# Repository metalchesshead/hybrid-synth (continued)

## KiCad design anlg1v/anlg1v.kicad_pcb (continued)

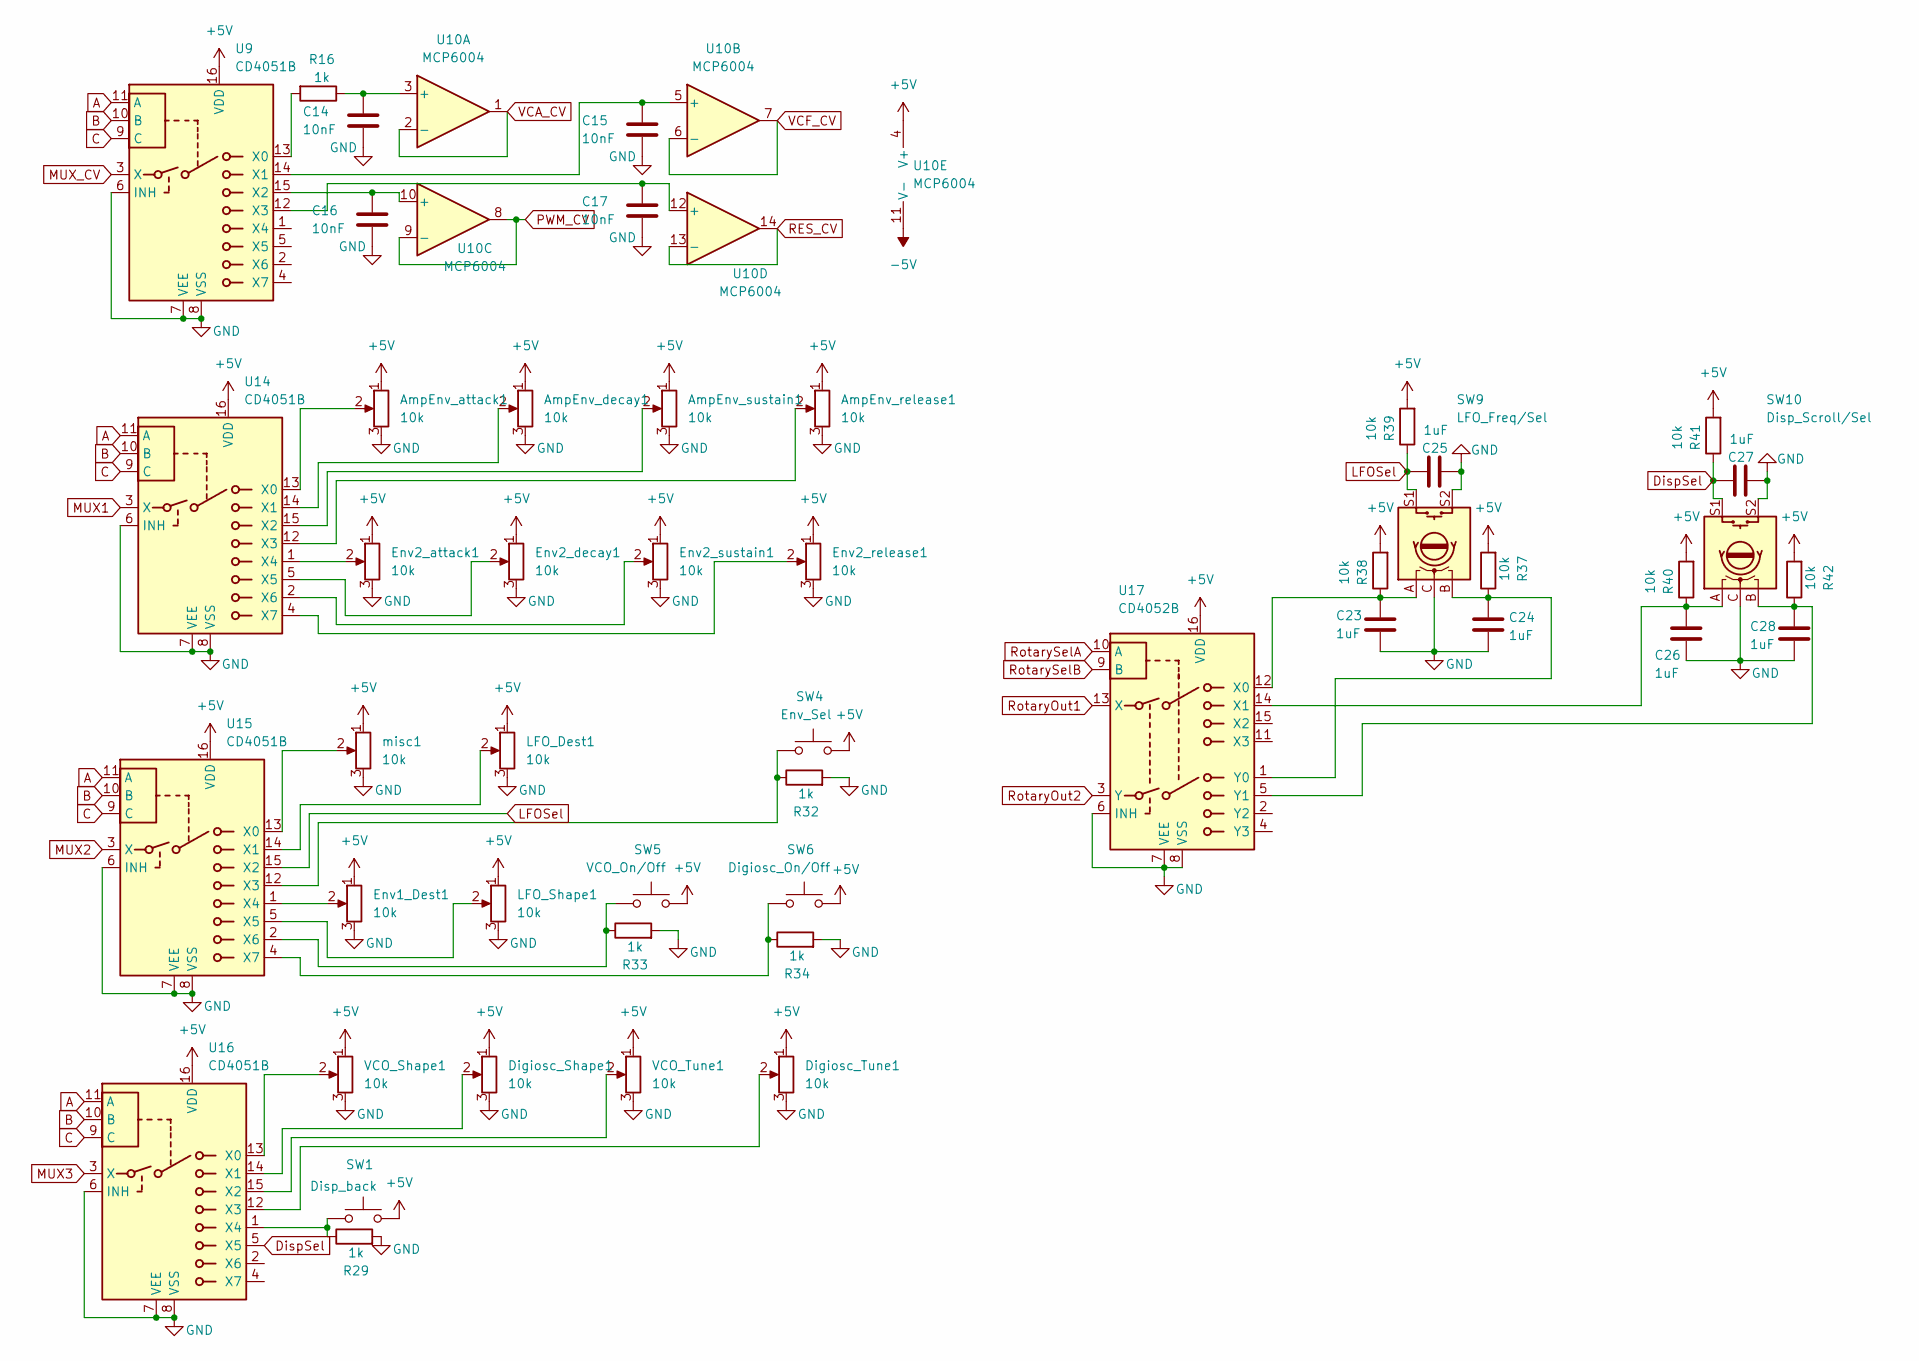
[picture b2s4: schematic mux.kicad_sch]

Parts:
AmpEnv_attack1: 10k; Potentiometer_Bourns_PTA3043_Single_Slide
AmpEnv_decay1: 10k; Potentiometer_Bourns_PTA3043_Single_Slide
AmpEnv_release1: 10k; Potentiometer_Bourns_PTA3043_Single_Slide
AmpEnv_sustain1: 10k; Potentiometer_Bourns_PTA3043_Single_Slide
C14, C15, C16, C17: 10nF; C_0603_1608Metric_Pad1.08x0.95mm_HandSolder
C23, C24, C25, C26, C27, C28: 1uF; C_0603_1608Metric_Pad1.08x0.95mm_HandSolder
Digiosc_Shape1: 10k; Potentiometer_Bourns_PTV09A-1_Single_Vertical
Digiosc_Tune1: 10k; Potentiometer_Bourns_PTV09A-1_Single_Vertical
Env1_Dest1: 10k; Potentiometer_Bourns_PTV09A-1_Single_Vertical
Env2_attack1, Env2_decay1, Env2_release1, Env2_sustain1: 10k; Potentiometer_Bourns_PTA3043_Single_Slide
LFO_Dest1: 10k; Potentiometer_Bourns_PTV09A-1_Single_Vertical
LFO_Shape1: 10k; Potentiometer_Bourns_PTV09A-1_Single_Vertical
R16, R29, R32, R33, R34: 1k; R_0603_1608Metric
R37, R38, R39, R40, R41, R42: 10k; R_0603_1608Metric
SW1: Disp_back; SW_TH_Tactile_Omron_B3F-102x
SW4: Env_Sel; SW_TH_Tactile_Omron_B3F-102x
SW5: VCO_On/Off; SW_TH_Tactile_Omron_B3F-102x
SW6: Digiosc_On/Off; SW_TH_Tactile_Omron_B3F-102x
SW9: LFO_Freq/Sel; RotaryEncoder_Bourns_Vertical_PEC12R-3x17F-Sxxxx
SW10: Disp_Scroll/Sel; RotaryEncoder_Bourns_Vertical_PEC12R-3x17F-Sxxxx
U9, U14, U15, U16: CD4051B; SOIC-16_3.9x9.9mm_P1.27mm
U10: MCP6004; SOIC-14_3.9x8.7mm_P1.27mm
U17: CD4052B; SOIC-16_3.9x9.9mm_P1.27mm
VCO_Shape1: 10k; Potentiometer_Bourns_PTV09A-1_Single_Vertical
VCO_Tune1: 10k; Potentiometer_Bourns_PTV09A-1_Single_Vertical
misc1: 10k; Potentiometer_Bourns_PTV09A-1_Single_Vertical

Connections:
+5V: AmpEnv_attack1.1, AmpEnv_decay1.1, AmpEnv_release1.1, AmpEnv_sustain1.1, Digiosc_Shape1.1, Digiosc_Tune1.1, Env1_Dest1.1, Env2_attack1.1, Env2_decay1.1, Env2_release1.1, Env2_sustain1.1, LFO_Dest1.1, LFO_Shape1.1, R37.2, R38.2, R39.2, R40.2, R41.2, R42.2, SW1.2, SW4.2, SW5.2, SW6.2, U9.16 (VDD), U10.4 (V+), U14.16 (VDD), U15.16 (VDD), U16.16 (VDD), U17.16 (VDD), VCO_Shape1.1, VCO_Tune1.1, misc1.1; also elsewhere on the board
-5V: U10.11 (V-); also elsewhere on the board
A: U9.11 (A), U14.11 (A), U15.11 (A), U16.11 (A); also elsewhere on the board
B: U9.10 (B), U14.10 (B), U15.10 (B), U16.10 (B); also elsewhere on the board
C: U9.9 (C), U14.9 (C), U15.9 (C), U16.9 (C); also elsewhere on the board
DispSel: C27.2, R41.1, SW10.S1, U16.5 (X5)
GND: AmpEnv_attack1.3, AmpEnv_decay1.3, AmpEnv_release1.3, AmpEnv_sustain1.3, C14.2, C15.2, C16.2, C17.2, C23.2, C24.2, C25.1, C26.2, C27.1, C28.2, Digiosc_Shape1.3, Digiosc_Tune1.3, Env1_Dest1.3, Env2_attack1.3, Env2_decay1.3, Env2_release1.3, Env2_sustain1.3, LFO_Dest1.3, LFO_Shape1.3, R29.2, R32.2, R33.2, R34.2, SW9.C, SW9.S2, SW10.C, SW10.S2, U9.6 (INH), U9.7 (VEE), U9.8 (VSS), U14.6 (INH), U14.7 (VEE), U14.8 (VSS), U15.6 (INH), U15.7 (VEE), U15.8 (VSS), U16.6 (INH), U16.7 (VEE), U16.8 (VSS), U17.6 (INH), U17.7 (VEE), U17.8 (VSS), VCO_Shape1.3, VCO_Tune1.3, misc1.3; also elsewhere on the board
LFOSel: C25.2, R39.1, SW9.S1, U15.15 (X2)
MUX1: U14.3 (X); also elsewhere on the board
MUX2: U15.3 (X); also elsewhere on the board
MUX3: U16.3 (X); also elsewhere on the board
MUX_CV: U9.3 (X); also elsewhere on the board
unnamed: R16.2, U9.13 (X0)
unnamed: C14.1, R16.1, U10.3 (+)
unnamed: C15.1, U9.14 (X1), U10.5 (+)
unnamed: C16.1, U9.15 (X2), U10.10 (+)
unnamed: C17.1, U9.12 (X3), U10.12 (+)
unnamed: AmpEnv_attack1.2, U14.13 (X0)
unnamed: AmpEnv_decay1.2, U14.14 (X1)
unnamed: AmpEnv_sustain1.2, U14.15 (X2)
unnamed: AmpEnv_release1.2, U14.12 (X3)
unnamed: Env2_attack1.2, U14.1 (X4)
unnamed: Env2_decay1.2, U14.5 (X5)
unnamed: Env2_sustain1.2, U14.2 (X6)
unnamed: Env2_release1.2, U14.4 (X7)
unnamed: U15.13 (X0), misc1.2
unnamed: LFO_Dest1.2, U15.14 (X1)
unnamed: R32.1, SW4.1, U15.12 (X3)
unnamed: Env1_Dest1.2, U15.1 (X4)
unnamed: LFO_Shape1.2, U15.5 (X5)
unnamed: R33.1, SW5.1, U15.2 (X6)
unnamed: R34.1, SW6.1, U15.4 (X7)
unnamed: U16.13 (X0), VCO_Shape1.2
unnamed: Digiosc_Shape1.2, U16.14 (X1)
unnamed: U16.15 (X2), VCO_Tune1.2
unnamed: Digiosc_Tune1.2, U16.12 (X3)
unnamed: R29.1, SW1.1, U16.1 (X4)
unnamed: C23.1, R38.1, SW9.A, U17.12 (X0)
unnamed: C26.1, R40.1, SW10.A, U17.14 (X1)
unnamed: C24.1, R37.1, SW9.B, U17.1 (Y0)
unnamed: C28.1, R42.1, SW10.B, U17.5 (Y1)
PWM_CV: U10.8, U10.9 (-)
RES_CV: U10.13 (-), U10.14; also elsewhere on the board
RotaryOut1: U17.13 (X); also elsewhere on the board
RotaryOut2: U17.3 (Y); also elsewhere on the board
RotarySelA: U17.10 (A); also elsewhere on the board
RotarySelB: U17.9 (B); also elsewhere on the board
VCA_CV: U10.1, U10.2 (-); also elsewhere on the board
VCF_CV: U10.6 (-), U10.7; also elsewhere on the board

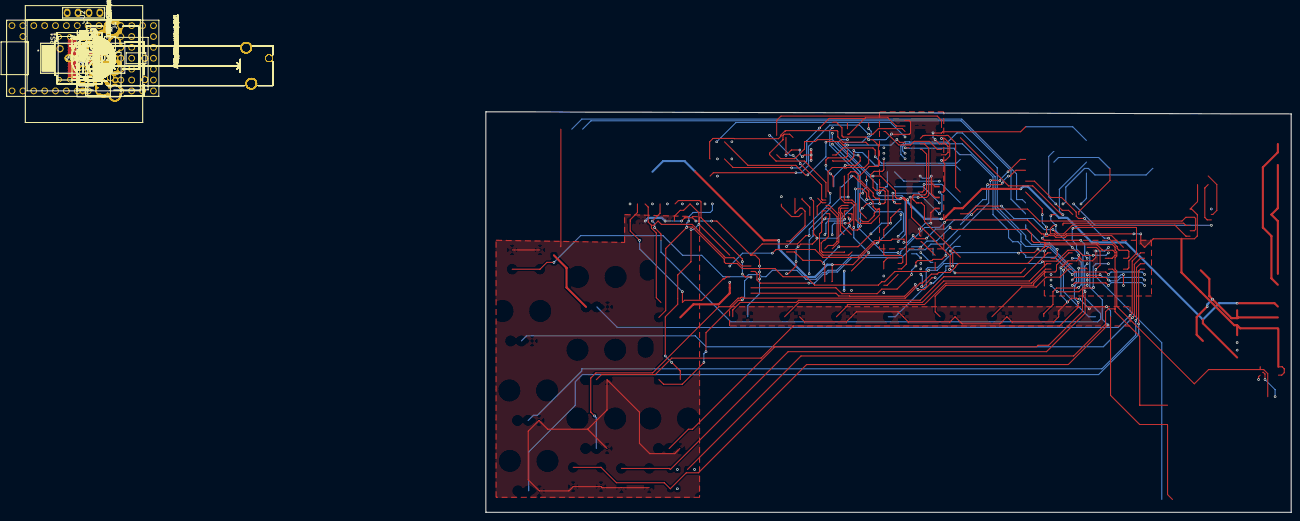
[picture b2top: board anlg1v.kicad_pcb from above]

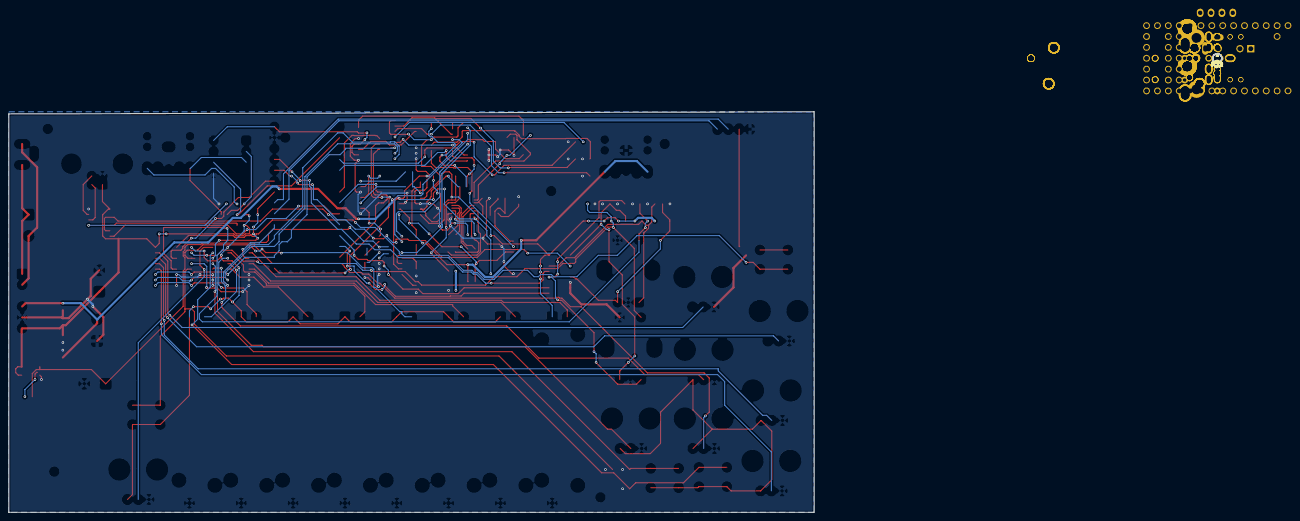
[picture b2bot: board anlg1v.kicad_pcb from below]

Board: 2 copper layers, 188.0 x 93.5 mm, 114 parts (6 on the bottom side), 109 nets.

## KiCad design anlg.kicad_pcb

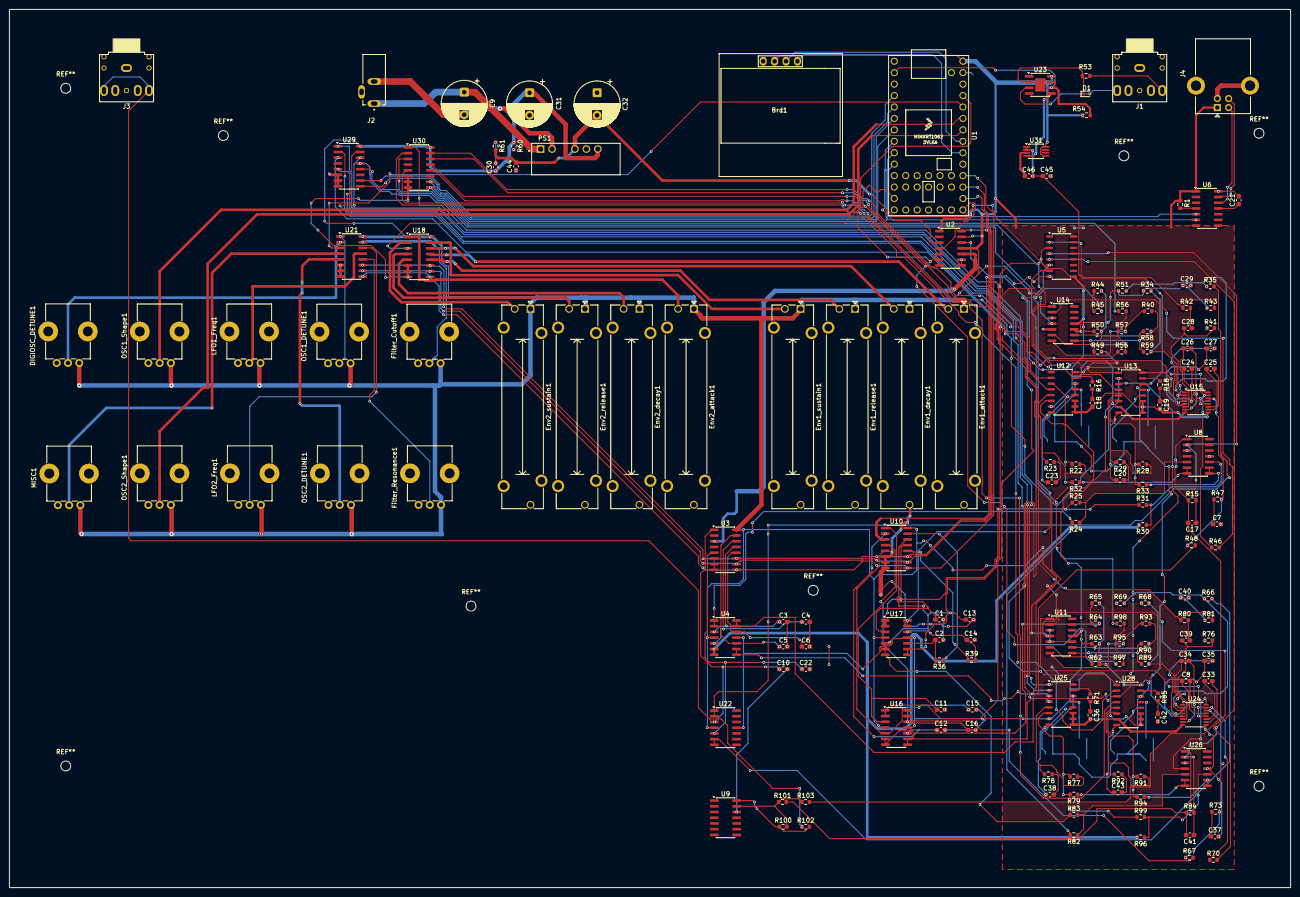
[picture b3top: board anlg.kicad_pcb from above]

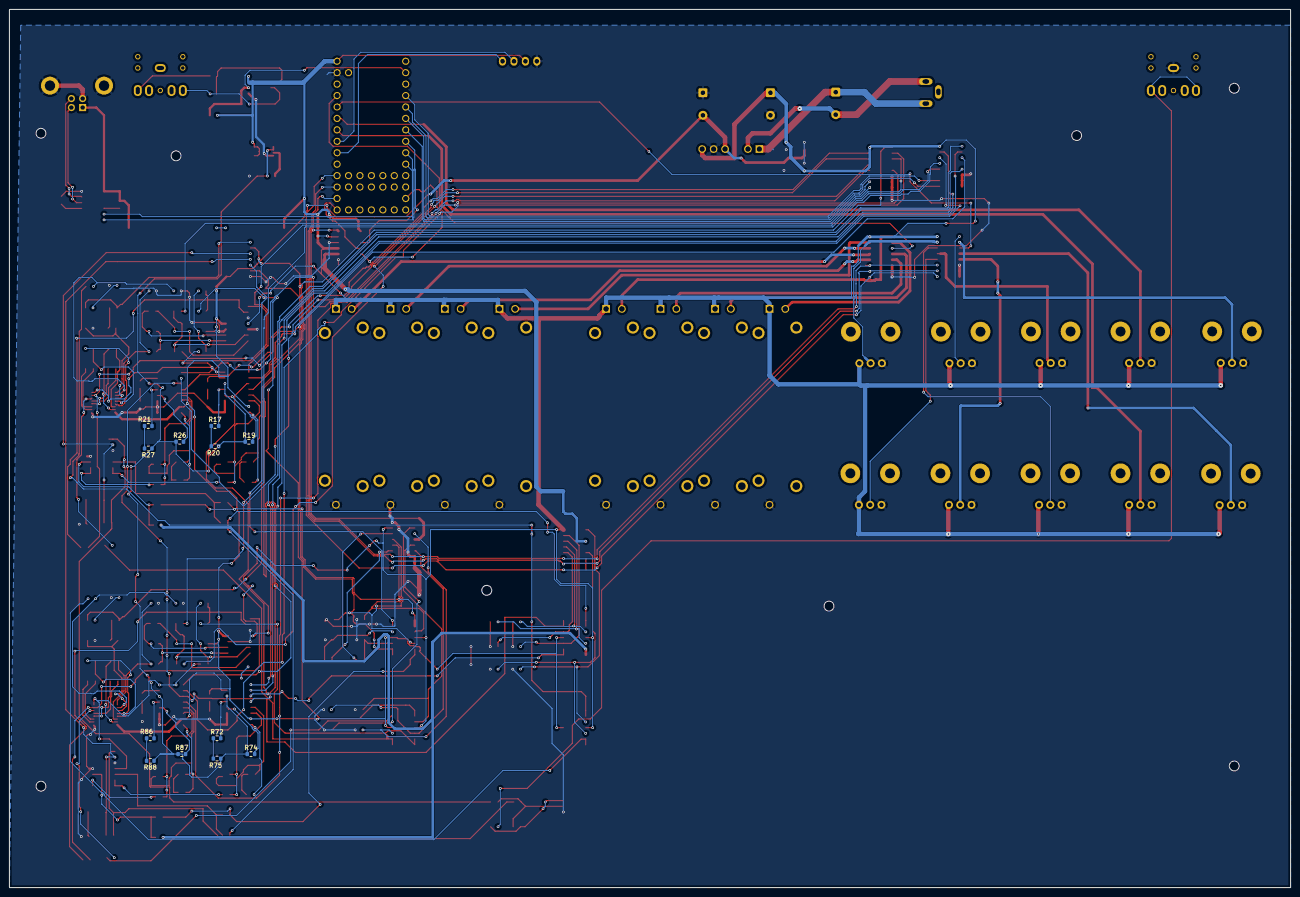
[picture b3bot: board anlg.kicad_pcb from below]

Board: 2 copper layers, 284.5 x 195.0 mm, 185 parts (12 on the bottom side), 195 nets.

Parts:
Brd1: SSD1306; 128x64OLED
C1, C2, C3, C4, C5, C6, C7, C10, C11, C12, C13, C14, C15, C16, C22, C37: 10nF; C_0603_1608Metric_Pad1.08x0.95mm_HandSolder
C8, C24, C25, C26, C33, C34: 6.8nF; C_0603_1608Metric_Pad1.08x0.95mm_HandSolder
C9: 1uF; CP_Radial_D10.0mm_P5.00mm
C17, C41, C46: 100pF; C_0603_1608Metric_Pad1.08x0.95mm_HandSolder
C18, C19, C20, C23, C36, C38, C42, C43: 2.2n; C_0603_1608Metric_Pad1.08x0.95mm_HandSolder
C21: 0.47; C_0603_1608Metric_Pad1.08x0.95mm_HandSolder
C27, C29, C35, C40: 560pF; C_0603_1608Metric_Pad1.08x0.95mm_HandSolder
C28, C39, C45: 10uF; C_0603_1608Metric_Pad1.08x0.95mm_HandSolder
C30, C44: 100nF; C_0603_1608Metric_Pad1.08x0.95mm_HandSolder
C31, C32: 10uF; CP_Radial_D10.0mm_P5.00mm
D1: 1N4148WT; D_SOD-523
DIGIOSC_DETUNE1: 10k; Potentiometer_Bourns_PTV09A-1_Single_Vertical
Env1_attack1, Env1_decay1, Env1_release1, Env1_sustain1, Env2_attack1, Env2_decay1, Env2_release1, Env2_sustain1: 10k; Potentiometer_Bourns_PTA3043_Single_Slide
Filter_Cutoff1: 10k; Potentiometer_Bourns_PTV09A-1_Single_Vertical
Filter_Resonance1: 10k; Potentiometer_Bourns_PTV09A-1_Single_Vertical
J1, J3: AudioJack3; PJ-307
J2: PJ-007; SAMESKY_PJ-007
J4: USB_B; USB_B_Lumberg_2411_02_Horizontal
LFO1_Freq1, LFO2_Freq1: 10k; Potentiometer_Bourns_PTV09A-1_Single_Vertical
MISC1: 10k; Potentiometer_Bourns_PTV09A-1_Single_Vertical
OSC1_DETUNE1, OSC1_Shape1, OSC2_DETUNE1, OSC2_Shape1: 10k; Potentiometer_Bourns_PTV09A-1_Single_Vertical
PS1: RD-0505D; CONV_RD-0505D
R1, R23, R29, R50, R63, R78, R92: 10k; R_0603_1608Metric
R15, R16, R18, R20, R27, R71, R75, R84, R85, R88: 20k; R_0603_1608Metric
R17, R21, R72, R86: 4.7k; R_0603_1608Metric
R19, R26, R74, R87: 499k; R_0603_1608Metric
R22, R28, R77, R91: 200k; R_0603_1608Metric
R24, R30, R49, R62, R82, R96: 30k; R_0603_1608Metric
R25, R31, R83, R99: 50k; R_0603_1608Metric
R32, R33, R48, R67, R79, R94: 22k; R_0603_1608Metric
R34, R51, R68, R69: 200; R_0603_1608Metric
R35, R66: 47k; R_0603_1608Metric
R36, R39, R42, R46, R59, R70, R80, R89, R102: 1k; R_0603_1608Metric
R40, R44, R45, R55, R56, R57, R58, R64, R65, R90, R93, R95, R97, R98, R100, R101, R103: 100k; R_0603_1608Metric
R41, R43, R76, R81: 5.1k; R_0603_1608Metric
R47, R73: 560; R_0603_1608Metric
R53, R60, R61: 220; R_0603_1608Metric
R54: 470; R_0603_1608Metric
U1: Teensy4.0; Teensy40
U2: MCP4922; SOIC-14_3.9x8.7mm_P1.27mm
U3, U10, U18, U21: CD4051B; SOIC-16_3.9x9.9mm_P1.27mm
U4, U8, U16, U17, U22, U26: MCP6004; SOIC-14_3.9x8.7mm_P1.27mm
U5: SSI2164; STC_SOP-16_3.9x9.9mm_P1.27mm
U6: MCP2221AxSL; SOIC-14_3.9x8.7mm_P1.27mm
U9, U11, U14: TL074; SOIC-14_3.9x8.7mm_P1.27mm
U12, U13, U25, U28: SSI2131; STC_SOP-16_3.9x9.9mm_P1.27mm
U15, U24: SSI2144; SSOP-16_3.9x4.9mm_P0.635mm
U23: 6N138; SOIC-8-1EP_3.9x4.9mm_P1.27mm_EP2.29x3mm
U29, U30: CD4052B; SOIC-16_3.9x9.9mm_P1.27mm
U31: LT1962-2.5; MSOP-8_3x3mm_P0.65mm

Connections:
+5V: Brd1.2 (VCC), C30.1, C31.1, DIGIOSC_DETUNE1.1, Env1_attack1.1, Env1_decay1.1, Env1_release1.1, Env1_sustain1.1, Env2_attack1.1, Env2_decay1.1, Env2_release1.1, Env2_sustain1.1, Filter_Cutoff1.1, Filter_Resonance1.1, J4.1 (VBUS), LFO1_Freq1.1, LFO2_Freq1.1, MISC1.1, OSC1_DETUNE1.1, OSC1_Shape1.1, OSC2_DETUNE1.1, OSC2_Shape1.1, PS1.6 (+VOUT), R1.1, R49.2, R54.1, R60.1, R62.2, U1.33 (VIN), U2.1 (Vdd), U2.11 (VrefB), U2.13 (VrefA), U3.16 (VDD), U4.4 (V+), U5.16 (V+), U6.1 (VDD), U8.4 (V+), U10.16 (VDD), U11.4 (V+), U12.16 (V+), U13.16 (V+), U14.4 (V+), U15.16 (V+), U16.4 (V+), U17.4 (V+), U18.16 (VDD), U21.16 (VDD), U22.4 (V+), U23.8 (VCC), U24.16 (V+), U25.16 (V+), U26.4 (V+), U28.16 (V+), U29.16 (VDD), U30.16 (VDD), U31.5 (~SHDN), U31.8 (IN)
-5V: C32.2, C44.2, PS1.4 (-VOUT), R50.1, R61.2, R63.1, U4.11 (V-), U5.9 (V-), U11.11 (V-), U12.7 (V-), U13.7 (V-), U14.11 (V-), U15.8 (V-), U16.11 (V-), U17.11 (V-), U22.11 (V-), U24.8 (V-), U25.7 (V-), U28.7 (V-)
A: U1.21 (14_A0_TX3_SPDIF_OUT), U3.11 (A), U10.11 (A), U18.11 (A), U21.11 (A)
B: U1.22 (15_A1_RX3_SPDIF_IN), U3.10 (B), U10.10 (B), U18.10 (B), U21.10 (B)
C: U1.23 (16_A2_RX4_SCL1), U3.9 (C), U10.9 (C), U18.9 (C), U21.9 (C)
DAC1: U2.14 (VA), U10.3 (X)
DAC2: U2.10 (VB), U3.3 (X)
DIGIOSC_1: R35.2, U22.1, U22.2 (-)
DIGIOSC_2: R66.2, U22.6 (-), U22.7
GND: Brd1.1 (GND), C1.2, C2.2, C3.2, C4.2, C5.2, C6.2, C7.2, C10.2, C11.2, C12.2, C13.2, C14.2, C15.2, C16.2, C18.2, C19.2, C21.2, C22.2, C29.2, C30.2, C31.2, C32.1, C36.2, C37.2, C40.2, C42.2, C44.1, C45.2, DIGIOSC_DETUNE1.3, Env1_attack1.3, Env1_decay1.3, Env1_release1.3, Env1_sustain1.3, Env2_attack1.3, Env2_decay1.3, Env2_release1.3, Env2_sustain1.3, Filter_Cutoff1.3, Filter_Resonance1.3, J3.S, J4.4 (GND), J4.5 (Shield), LFO1_Freq1.3, LFO2_Freq1.3, MISC1.3, OSC1_DETUNE1.3, OSC1_Shape1.3, OSC2_DETUNE1.3, OSC2_Shape1.3, PS1.5 (COM), R34.1, R41.1, R51.1, R60.2, R61.1, R68.1, R69.1, R76.1, U1.32 (GND), U2.8 (~LDAC), U2.9 (~SHDN), U2.12 (Vss), U5.8 (GND), U6.14 (VSS), U8.3 (+), U8.11 (V-), U9.12 (+), U10.6 (INH), U10.7 (VEE), U10.8 (VSS), U11.3 (+), U11.5 (+), U11.10 (+), U12.9 (GND), U12.10 (HARD_SYNC), U12.11 (SOFT_SYNC), U13.9 (GND), U13.10 (HARD_SYNC), U13.11 (SOFT_SYNC), U14.3 (+), U14.5 (+), U14.10 (+), U15.9 (GND), U18.6 (INH), U18.7 (VEE), U18.8 (VSS), U21.6 (INH), U21.7 (VEE), U21.8 (VSS), U23.5 (GND), U24.9 (GND), U25.9 (GND), U25.10 (HARD_SYNC), U25.11 (SOFT_SYNC), U26.3 (+), U26.11 (V-), U28.9 (GND), U28.10 (HARD_SYNC), U28.11 (SOFT_SYNC), U29.6 (INH), U29.7 (VEE), U29.8 (VSS), U30.6 (INH), U30.7 (VEE), U30.8 (VSS), U31.4 (GND)
unnamed: Brd1.3 (SCL), U1.26 (19_A5_SCL0)
unnamed: Brd1.4 (SDA), U1.25 (18_A4_SDA0)
unnamed: C7.1, R47.1
unnamed: C18.1, R16.2
unnamed: C19.1, R18.2
unnamed: C20.2, R29.1
unnamed: C23.2, R23.1
unnamed: C28.2, R42.2
unnamed: C29.1, R43.1
unnamed: C36.1, R71.2
unnamed: C37.1, R73.1
unnamed: C38.2, R78.1
unnamed: C39.2, R80.2
unnamed: C40.1, R81.1
unnamed: C42.1, R85.2
unnamed: C43.2, R92.1
unnamed: D1.2 (A), J1.T, U23.3 (C2)
unnamed: D1.1 (K), R53.1, U23.2 (C1)
unnamed: J1.R, R53.2
unnamed: J3.R, J3.T, R102.1
unnamed: J4.3 (D+), U6.13 (D+)
unnamed: J4.2 (D-), U6.12 (D-)
unnamed: C9.1, J2.1, PS1.1 (+VIN)
unnamed: C9.2, J2.2, PS1.2 (-VIN)
unnamed: R17.1, R20.2
unnamed: R21.1, R27.2
unnamed: R40.1, R57.2, U14.7
unnamed: R42.1, R43.2, U5.2
unnamed: R44.2, R49.1, R50.2
unnamed: R58.2, R59.1, U14.8
unnamed: R62.1, R63.2, R65.2
unnamed: R72.1, R75.2
unnamed: R80.1, R81.2, U5.7
unnamed: R86.1, R88.2
unnamed: R89.1, R90.2, U11.8
unnamed: R93.1, R95.2, U11.7
unnamed: R100.1, R102.2, U9.14
unnamed: R54.2, U1.2 (0_RX1_CRX2_CS1), U23.6 (VO2)
unnamed: U1.8 (6_OUT1D), U2.3 (~CS)
unnamed: U1.13 (11_MOSI_CTX1), U2.5 (SDI)
unnamed: U1.20 (13_SCK_CRX1_LED), U2.4 (SCK)
unnamed: OSC2_Shape1.2, U1.27 (20_A6_TX5_LRCLK1)
unnamed: OSC1_Shape1.2, U1.28 (21_A7_RX5_BCLK1)
unnamed: U3.6 (INH), U3.7 (VEE), U3.8 (VSS)
unnamed: C3.1, U3.13 (X0), U4.3 (+)
unnamed: C4.1, U3.14 (X1), U4.5 (+)
unnamed: C5.1, U3.15 (X2), U4.10 (+)
unnamed: C6.1, U3.12 (X3), U4.12 (+)
unnamed: C21.1, U6.11 (VUSB)
unnamed: R1.2, U6.4 (~RST)
unnamed: C17.1, R15.2, U5.4, U8.2 (-)
unnamed: R24.1, R25.2, U8.5 (+)
unnamed: R32.1, U8.6 (-), U8.7
unnamed: R30.1, R31.2, U8.10 (+)
unnamed: R33.1, U8.8, U8.9 (-)
unnamed: R100.2, R101.1, R103.1, U9.13 (-)
unnamed: C1.1, U10.13 (X0), U17.3 (+)
unnamed: C13.1, U10.14 (X1), U17.5 (+)
unnamed: R36.1, U10.15 (X2)
unnamed: R39.1, U10.12 (X3)
unnamed: C11.1, U10.1 (X4), U16.3 (+)
unnamed: C15.1, U10.5 (X5), U16.5 (+)
unnamed: C12.1, U10.2 (X6), U16.10 (+)
unnamed: C16.1, U10.4 (X7), U16.12 (+)
unnamed: R64.1, R65.1, R70.2, U11.2 (-)
unnamed: R95.1, R97.2, R98.2, U11.6 (-)
unnamed: R90.1, R93.2, U11.9 (-)
unnamed: R16.1, U12.15 (BW_COMP)
unnamed: R22.2, R32.2, U12.6 (EXPO_FREQ)
unnamed: R17.2, U12.13 (EXPO_SCALE)
unnamed: R22.1, R23.2, U12.5 (HF_TRACK)
unnamed: R19.2, U12.12 (LIN_FREQ)
unnamed: C23.1, U12.8 (TCAP)
unnamed: R18.1, U13.15 (BW_COMP)
unnamed: R28.2, R33.2, U13.6 (EXPO_FREQ)
unnamed: R21.2, U13.13 (EXPO_SCALE)
unnamed: R28.1, R29.2, U13.5 (HF_TRACK)
unnamed: R26.2, U13.12 (LIN_FREQ)
unnamed: C20.1, U13.8 (TCAP)
unnamed: R44.1, R45.1, R46.2, U14.2 (-)
unnamed: R55.2, R56.2, R57.1, U14.6 (-)
unnamed: R40.2, R58.1, U14.9 (-)
unnamed: C24.1, U15.13 (C1A)
unnamed: C24.2, U15.12 (C1B)
unnamed: C25.1, U15.11 (C2A)
unnamed: C25.2, U15.10 (C2B)
unnamed: C26.1, U15.6 (C3A)
unnamed: C26.2, U15.7 (C3B)
unnamed: C27.1, U15.4 (C4A)
unnamed: C27.2, U15.5 (C4B)
unnamed: R46.1, U14.1, U15.15 (FREQ_CTRL)
unnamed: C28.1, R41.2, U15.3 (OUT)
unnamed: R47.2, R48.1, U15.14 (Q_CTRL)
unnamed: R35.1, R51.2, U15.2 (SIG_IN-)
unnamed: C2.1, R36.2, U17.10 (+)
unnamed: C14.1, R39.2, U17.12 (+)
unnamed: Env1_attack1.2, U18.13 (X0)
unnamed: Env1_decay1.2, U18.14 (X1)
unnamed: Env1_sustain1.2, U18.15 (X2)
unnamed: Env1_release1.2, U18.12 (X3)
unnamed: Env2_attack1.2, U18.1 (X4)
unnamed: Env2_decay1.2, U18.5 (X5)
unnamed: Env2_sustain1.2, U18.2 (X6)
unnamed: Env2_release1.2, U18.4 (X7)
unnamed: LFO1_Freq1.2, U21.13 (X0)
unnamed: LFO2_Freq1.2, U21.14 (X1)
unnamed: Filter_Cutoff1.2, U21.15 (X2)
unnamed: Filter_Resonance1.2, U21.12 (X3)
unnamed: OSC1_DETUNE1.2, U21.1 (X4)
unnamed: OSC2_DETUNE1.2, U21.5 (X5)
unnamed: DIGIOSC_DETUNE1.2, U21.2 (X6)
unnamed: MISC1.2, U21.4 (X7)
unnamed: C10.1, U3.1 (X4), U22.3 (+)
unnamed: C22.1, U3.5 (X5), U22.5 (+)
unnamed: C8.1, U24.13 (C1A)
unnamed: C8.2, U24.12 (C1B)
unnamed: C33.1, U24.11 (C2A)
unnamed: C33.2, U24.10 (C2B)
unnamed: C34.1, U24.6 (C3A)
unnamed: C34.2, U24.7 (C3B)
unnamed: C35.1, U24.4 (C4A)
unnamed: C35.2, U24.5 (C4B)
unnamed: R70.1, U11.1, U24.15 (FREQ_CTRL)
unnamed: C39.1, R76.2, U24.3 (OUT)
unnamed: R67.1, R73.2, U24.14 (Q_CTRL)
unnamed: R66.1, R69.2, U24.2 (SIG_IN-)
unnamed: R71.1, U25.15 (BW_COMP)
unnamed: R77.2, R79.2, U25.6 (EXPO_FREQ)
unnamed: R72.2, U25.13 (EXPO_SCALE)
unnamed: R77.1, R78.2, U25.5 (HF_TRACK)
unnamed: R74.2, U25.12 (LIN_FREQ)
unnamed: C38.1, U25.8 (TCAP)
unnamed: C41.1, R84.2, U5.5, U26.2 (-)
unnamed: R82.1, R83.2, U26.5 (+)
unnamed: R79.1, U26.6 (-), U26.7
unnamed: R96.1, R99.2, U26.10 (+)
unnamed: R94.1, U26.8, U26.9 (-)
unnamed: R85.1, U28.15 (BW_COMP)
unnamed: R91.2, R94.2, U28.6 (EXPO_FREQ)
unnamed: R86.2, U28.13 (EXPO_SCALE)
unnamed: R91.1, R92.2, U28.5 (HF_TRACK)
unnamed: R87.2, U28.12 (LIN_FREQ)
unnamed: C43.1, U28.8 (TCAP)
unnamed: C46.1, U31.3 (BYP)
OSC1V1PULSE1: U12.2 (PULSE_OUT), U29.14 (X1)
OSC1V1SAW: U12.1 (SAW_OUT), U29.12 (X0)
OSC1V1TRI: U12.4 (TRI_OUT), U29.15 (X2)
OSC1V1_OUT: R55.1, U29.3 (Y)
OSC1V2PULSE1: U25.2 (PULSE_OUT), U29.5 (Y1)
OSC1V2SAW: U25.1 (SAW_OUT), U29.1 (Y0)
OSC1V2TRI: U25.4 (TRI_OUT), U29.2 (Y2)
OSC1V2_OUT: R98.1, U29.13 (X)
OSC1_TUNE: R24.2, R82.2, U4.1, U4.2 (-)
OSC2V1PULSE1: U13.2 (PULSE_OUT), U30.14 (X1)
OSC2V1SAW: U13.1 (SAW_OUT), U30.12 (X0)
OSC2V1TRI: U13.4 (TRI_OUT), U30.15 (X2)
OSC2V1_OUT: R56.1, U30.3 (Y)
OSC2V2PULSE1: U28.2 (PULSE_OUT), U30.5 (Y1)
OSC2V2SAW: U28.1 (SAW_OUT), U30.1 (Y0)
OSC2V2TRI: U28.4 (TRI_OUT), U30.2 (Y2)
OSC2V2_OUT: R97.1, U30.13 (X)
OSC2_TUNE: R30.2, R96.2, U4.6 (-), U4.7
OSCv1SUM_OUT: R34.2, R59.2, U15.1 (SIG_IN+)
OSCv2SUM_OUT: R68.2, R89.2, U24.1 (SIG_IN+)
POTS_IN: U1.30 (23_A9_CRX1_MCLK1), U18.3 (X)
POTS_IN2: U1.29 (22_A8_CTX1), U21.3 (X)
PWMCV_1: U4.8, U4.9 (-), U12.3 (PWM_CTRL), U25.3 (PWM_CTRL)
PWMCV_2: U4.13 (-), U4.14, U13.3 (PWM_CTRL), U28.3 (PWM_CTRL)
REF2V5: C45.1, C46.2, R19.1, R20.1, R26.1, R27.1, R74.1, R75.1, R87.1, R88.1, U12.14 (VREF), U13.14 (VREF), U25.14 (VREF), U28.14 (VREF), U31.1 (OUT), U31.2 (SENSE)
RES_CV1: R48.2, U16.8, U16.9 (-)
RES_CV2: R67.2, U16.13 (-), U16.14
USB_rx: U1.10 (8_TX2_IN1), U6.5 (URx)
USB_tx: U1.9 (7_RX2_OUT1A), U6.6 (UTx)
V1_OUT: C17.2, R15.1, R103.2, U8.1
V2_OUT: C41.2, R84.1, R101.2, U26.1
VCA_CV1: U5.3, U17.8, U17.9 (-)
VCA_CV2: U5.6, U17.13 (-), U17.14
VCF_CV1: R45.2, U16.1, U16.2 (-)
VCF_CV2: R64.2, U16.6 (-), U16.7
VCO_CV1: R25.1, R31.1, U17.1, U17.2 (-)
VCO_CV2: R83.1, R99.1, U17.6 (-), U17.7
WAVESELA1: U1.4 (2_OUT2), U29.10 (A)
WAVESELA2: U1.6 (4_BCLK2), U30.10 (A)
WAVESELB1: U1.5 (3_LRCLK2), U29.9 (B)
WAVESELB2: U1.7 (5_IN2), U30.9 (B)

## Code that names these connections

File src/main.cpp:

#include <MIDI.h>
#include <SPI.h>
#include <Arduino.h>
#include <Wire.h>

#include <EEPROM.h>
#include "header.h"
#include "lut.h"
#include "displaystuff.h"
#include <HardwareSerial.h>
#include <usb_serial.h>
#include <Adafruit_SSD1306.h>

#include <Audio.h>

MIDI_CREATE_INSTANCE(HardwareSerial, Serial1, MIDI); 


#include <Audio.h>
#include <Wire.h>
#include <SPI.h>
#include <SD.h>
#include <SerialFlash.h>

// GUItool: begin automatically generated code
AudioSynthNoisePink      pink1;          //xy=192.20000076293945,360.2000026702881
AudioSynthNoiseWhite     noise1;         //xy=193.20000076293945,317.2000026702881
AudioSynthWaveform       waveform1;      //xy=219.20000076293945,265.1999702453613
AudioMixer4              mixer1;         //xy=365.20000076293945,330.20000076293945
AudioOutputPT8211        pt8211_output;  //xy=529.1999740600586,327.19997215270996
AudioConnection          patchCord1(pink1, 0, mixer1, 2);
AudioConnection          patchCord2(noise1, 0, mixer1, 1);
AudioConnection          patchCord3(waveform1, 0, mixer1, 0);
AudioConnection          patchCord4(mixer1, 0, pt8211_output, 0);
AudioConnection          patchCord5(mixer1, 0, pt8211_output, 1);
AudioControlSGTL5000     sgtl5000_1;     //xy=241.19998931884766,423.2000045776367
// GUItool: end automatically generated code

#define DISPLAY_WIDTH    128
#define DISPLAY_HEIGHT   64
Adafruit_SSD1306 display(DISPLAY_WIDTH, DISPLAY_HEIGHT, &Wire, -1);
int rotaryAin, rotaryBin;
int rotaryCount = 0;

int lfodestbuff = 0;
 int dacData;
 int dacthing;
int i = 0;
int note1;
int iprev = 0;
int returndispbuff = 0;
// int jprev = 0;
 uint16_t uartdata[256];
 int eedata[256];
const float sampleRate = 44100.0;    // sample rate 44.1KHz
volatile int phInc, phInc2, phIncLFO;                  // dds phase increment
volatile unsigned long phAcc, phAcc2, phAccLFO;        // dds phase accumulator
unsigned long tuningWord, tuningWord2, tuningWordLFO;            // dds tuning word (M)
float lfoFreq = 0;
float fOut, fOut2;      
byte tableAddrWidth;
int rec = '0';
uint8_t bigserialbuffer[4096];
uint8_t numBits(uint32_t num) {
 uint8_t width = 32;                // maximum bit width of number being tested
 while (width) {
    width--;
    if (num & (1 << width)) break;  // look for bit position of first "1" from MSB toward LSB
  }                                 // that eliminates leading zeroes and the number bit width is found
 return (width+1);
 }
 void lfo() {
  tableAddrWidth = numBits(256 - 1); 
  tuningWordLFO = pow(2, 32) * lfoFreq / sampleRate;
  phAccLFO += tuningWordLFO;
  phIncLFO = phAccLFO >> (32 - tableAddrWidth);
  dacData = (lfothingy[phIncLFO] >> 1);
}

void setup() {
    // Wire.setClock(1000000);
    // Wire.begin();
            Serial.begin(31250);

    Serial3.begin(31250);
    Serial3.addMemoryForRead(&bigserialbuffer, sizeof(bigserialbuffer)); //resizebuffer
        Wire.begin();
    Wire.setClock(400000);
    delay(1000);
    dma.begin(true);

    delay(20);

    // Initialize OLED using DMA
    oledInitDMA();
    oledClearDMA();
drawcurrentwave(lu67, lutSaw);
 //dmaPrint("HELLO WORLD", 0, 0);
  AudioMemory(20);
  sgtl5000_1.enable();
  sgtl5000_1.volume(1);
  EEPROM.get(0, lu67);
  waveform1.arbitraryWaveform(lu67, 1000);
  waveform1.begin(WAVEFORM_ARBITRARY);


  MIDI.setHandleNoteOn(myNoteOn);
  MIDI.setHandleNoteOff(myNoteOff);
  MIDI.begin(MIDI_CHANNEL_OMNI);

    SPI.begin();
    pinMode(1, OUTPUT); //CV_INH
    pinMode(2, OUTPUT); //A
    pinMode(3, OUTPUT); //B
    pinMode(4, OUTPUT); //C
    pinMode(5, OUTPUT); //wavesel A
    pinMode(8, OUTPUT); //wavesel B

    pinMode(6, OUTPUT); //CS1
    pinMode(12, OUTPUT);

    pinMode(22, INPUT); //mux2
    pinMode(17, INPUT); //mux1
    pinMode(16, INPUT); //mux3

    pinMode(9, OUTPUT); //RotaryselA
    pinMode(10, OUTPUT); //RotaryselB
  SPI.setMOSI(11);
  SPI.setSCK(13);

    
//displaystart();
//drawcurrentwave(lu67, lut);

}


void envelopee() {


       CV0=muxA0;
  alpha1=0.999*cos((1023-CV0)/795);
  alpha1=sqrt(alpha1);  

//   alphaA1=0.999*cos((1023-CV0)/795);
//   alphaA1=sqrt(alphaA1);  
 
 // CV1=analogRead(1);      
 CV1 = muxA1;                // get the release pole location
  alpha2=0.999*cos((1023-CV1)/795);
  alpha2=sqrt(alpha2);  
  
//   alphaA2=0.999*cos((1023-CV1)/795);
//   alphaA2=sqrt(alphaA2); 
  
 //CV2=mux2A;                     // get the (integer) sustain level
 CV2 = round((drive/1023))*muxA2 + 610;
  sustain=CV2;
//   sustainA=CV2<<2;



  //CV3=analogRead(3);                     // get the release pole location (potentially closer to 1.0)
  CV3 = muxA3;
  alpha3=0.99999*cos((1023-CV3)/795);
  alpha3=sqrt(alpha3);

//   alphaA3=0.99999*cos((1023-CV3)/795);
//   alphaA3=sqrt(alphaA3);
envelope= ((1.0-alpha)*drive+alpha*envelope);
//dacWrite2(round(2700-envelope));
if (envelope<4.0) {
  envelope = 0.0;
}

if(decay == false && ((envelope>=(drive-3) && drive==21*velocity1))){// if we are in attack phase and we've reached envelope >4000 with drive= 4096, we must be at the end of attack phase
                                                            // so switch to decay...
      decay = true;                                         // set decay flag
      drive=sustain;                                  // drive toward sustain level
      alpha=alpha2;                                         // and set 'time constant' alpha2 for decay phase
      }



}
void serialstuffs() {

  while (Serial3.available()>=514) {
        byte startbit2 = Serial3.read();

    byte startbit1 = Serial3.read();
    if (((startbit1 << 8) | startbit2) !=5) {
      Serial.println("error");
    }
  
  //Serial.println("23232");

 for (i =0; i<256; i++){
byte low = Serial3.read();
   byte high = Serial3.read();
   
//uartdata[i + iprev ]= (low << 8) | high;
uartdata[i]= (high << 8) | low;


  }
  rec = rec + 1;
  //Serial3.println((uint8_t)rec);
iprev = iprev + 32;

//Serial.println((iprev));

}


 
if (iprev>0) {

  for (int j = 0; j<256; j++) {
    
    Serial.println(uartdata[j]);
lu67[j] = uartdata[j];

  }
  EEPROM.put(0, lu67);
    waveform1.arbitraryWaveform(lu67, 1000);
  waveform1.begin(WAVEFORM_ARBITRARY);
  //eepromwrite(0, eedata, 256);
  iprev = 0;
  oledClearDMA();
  drawcurrentwave(lu67, lutSaw);
}  

}
void loop() {

  digitalWrite(9, LOW);
  digitalWrite(10, LOW);
     if (muxC6 != rotaryAin){     
     // If the outputB state is different to the outputA state, that means the encoder is rotating clockwise
     if (muxC7 != muxC6) { 
       rotaryCount ++;
     } else {
       rotaryCount --;
     }
     Serial.print("Position: ");
     Serial.println(rotaryCount);
   } 
   rotaryAin = muxC6; // Updates the previous state of the outputA with the current state
 if (rotaryCount>=100){
  rotaryCount = 100;
 }
 if (rotaryCount<=0) {
  rotaryCount = 0;
 }
 lfoFreq = rotaryCount;

    if (!ismoving) {
              if (movebuff ==1) {
                oledClearDMA();
                movebuff = 0;
                    if (muxC0<100) {
drawcurrentwave(lu67, lu67);}

else if (muxC0>=100 && muxC0<500)
{
  drawcurrentwave(lu67, lutSaw);
}
else if (muxC0>=500 && muxC0 <750) {
  drawcurrentwave(lu67, lutSqr);

}
else if (muxC0>=750) {
  drawcurrentwave(lu67, lutTri);
}
                
              }
  
  }
 // dmatst();

  // for (int i=0; i<256; i++){
  //   Serial.print(32768-(lu67[i] + lut[i])/2);
  //   Serial.print(",");

  // }
  // Serial.println();
  //   Serial.println("------------------------------");
// if (ismoving == true){ 
//   //attack();
//   returndispbuff +=1;
// }
// else {
//   if (returndispbuff >0) {
//     //homescreen();
//     //drawcurrentwave(lu67, lut);
//     returndispbuff = 0;
//   }
// }
  serialstuffs();
  if (muxC1<100) {
waveform1.amplitude(0);

}
else {
waveform1.amplitude(0.9);
}
      
   waveform1.frequency(freq1);
MIDI.read();
lfo();
//Serial.println(dacData);
//dacthing =round(((float)dacData/16384)*note1*14.67);
dacthing =round(note1*14.89 + int(100*(float)muxC2/1023 - 50));
if (muxC0<100) {
digitalWrite(5, HIGH);
digitalWrite(8, HIGH);
}
else if (muxC0>=100 && muxC0<500)
{
  digitalWrite(5, LOW);
digitalWrite(8, LOW);
}
else if (muxC0>=500 && muxC0 <750) {
  digitalWrite(5, HIGH);
digitalWrite(8, LOW);
}
else if (muxC0>=750) {
  digitalWrite(5, LOW);
digitalWrite(8, HIGH);
}

mux();
envelopee();
  //   waveform1.amplitude(tempamp);
  //  waveform1.frequency(freq1);
//dacWrite1(dacthing, 0);
//dacWrite1(430, 1);

//digitalWrite(1, HIGH); //CV_INH

//digitalWrite(1, LOW); //CV_INH
// muxA0 = analogRead(17);
// muxB0 = analogRead(20);
//delayMicroseconds(5);



}

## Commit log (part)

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2026-05-21 Add initial styles for the board element
2026-05-31 Display number of drawn coordinates in draw function
    Update draw function to display the number of coordinates drawn.
2026-06-27 Refactor DAC pin usage and update mux logic
2026-06-27 Add additional analog reads for mux channels
